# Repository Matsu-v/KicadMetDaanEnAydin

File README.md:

# Kicad Met Daan & Aydin

- x daaN

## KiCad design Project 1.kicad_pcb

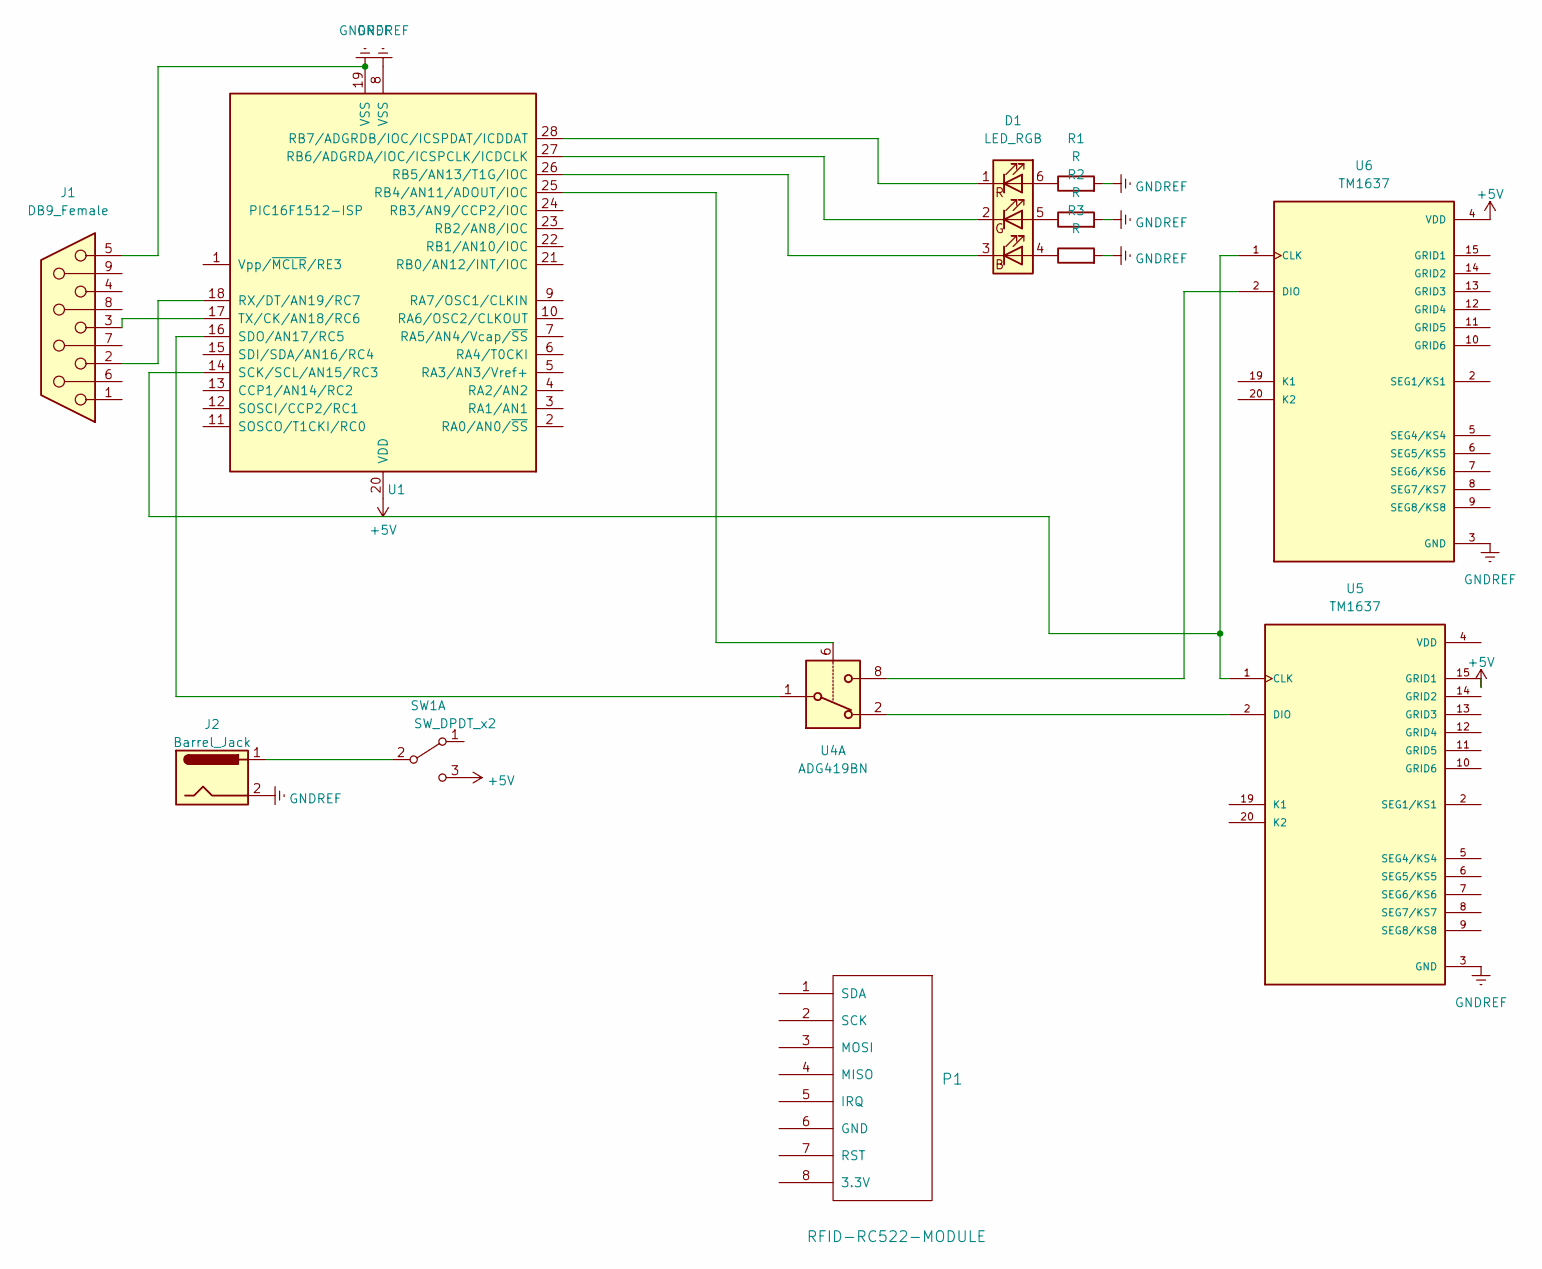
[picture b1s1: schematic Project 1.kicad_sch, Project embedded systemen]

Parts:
D1: LED_RGB; LED_Avago_PLCC6_3x2.8mm
J1: DB9_Female; DSUB-9_Female_Vertical_P2.77x2.84mm
J2: Barrel_Jack; BarrelJack_CLIFF_FC681465S_SMT_Horizontal
P1: RFID-RC522-MODULE; PinHeader_1x08_P1.27mm_Vertical
R1, R2, R3: R; R_0201_0603Metric
SW1: SW_DPDT_x2; SW_CuK_JS202011AQN_DPDT_Angled
U1: PIC16F1512-ISP; DIP-28_W7.62mm_Socket
U4: ADG419BN; DIP-8_W7.62mm
U5, U6: TM1637; PinHeader_1x04_P1.27mm_Vertical; PARTREV v2.5

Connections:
+5V: SW1.3 (C), U1.20 (VDD), U6.4 (VDD)
GNDREF: J1.5, J2.2, R1.2, R2.2, R3.2, U1.8 (VSS), U1.19 (VSS), U5.3 (GND), U6.3 (GND)
unnamed: D1.4 (BA), R3.1
unnamed: D1.5 (GA), R2.1
unnamed: D1.6 (RA), R1.1
unnamed: J1.2, U1.18 (RX/DT/AN19/RC7)
unnamed: J1.3, U1.17 (TX/CK/AN18/RC6)
unnamed: J2.1, SW1.2 (B)
unnamed: U1.14 (SCK/SCL/AN15/RC3), U5.1 (CLK), U6.1 (CLK)
unnamed: U1.16 (SDO/AN17/RC5), U4.1
unnamed: U1.25 (RB4/AN11/ADOUT/IOC), U4.6
unnamed: D1.3 (BK), U1.26 (RB5/AN13/T1G/IOC)
unnamed: D1.2 (GK), U1.27 (RB6/ADGRDA/IOC/ICSPCLK/ICDCLK)
unnamed: D1.1 (RK), U1.28 (RB7/ADGRDB/IOC/ICSPDAT/ICDDAT)
unnamed: U4.2, U5.2 (DIO)
unnamed: U4.8, U6.2 (DIO)

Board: 2 copper layers, 12 parts (0 on the bottom side), 16 nets, no tracks yet.

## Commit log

2022-10-27 Add begin files
2022-10-27 Create README.md
    bier
2022-10-27 Add files via upload
    prut met peren
2022-11-25 Nieuwe tekening begin nieuw schema
    Nieuwe tekening begin nieuw schema
2022-11-25 ZElfde
2022-12-09 Update README.md
    - layout update
